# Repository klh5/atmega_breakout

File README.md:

# atmega_breakout
Breaking out the ATMega328P

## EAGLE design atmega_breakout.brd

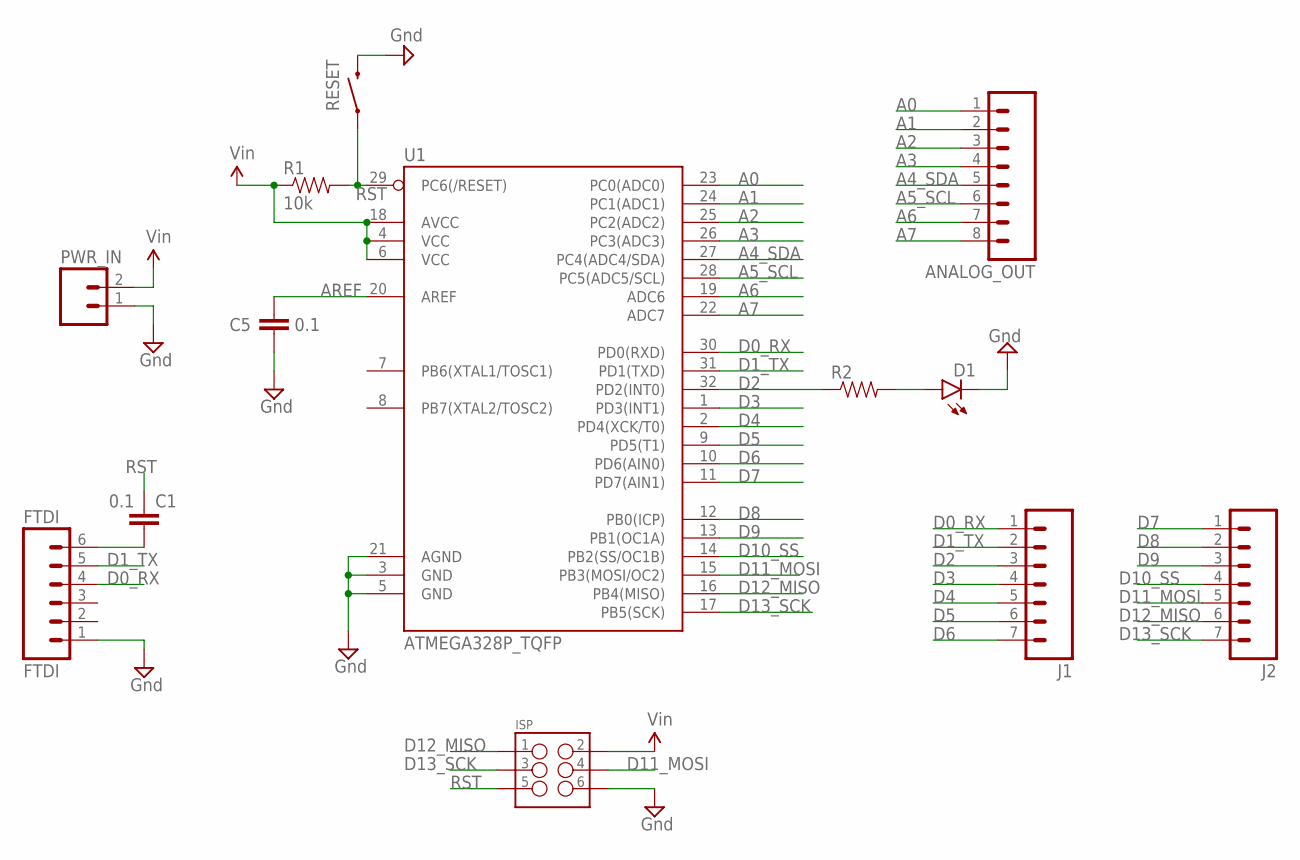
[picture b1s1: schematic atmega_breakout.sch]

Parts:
ANALOG_OUT: M08; 1X08_ROUND
C1, C5: 0.1; 1206
D1: LED1206; LED-1206
FTDI: FTDI; 1X06
ISP: M03X22X3_SILK_MALE_PTH; 2X3
J1, J2: M07; 1X07
PWR_IN: M02PTH; 1X02
R1: 10k; 1206
R2: RESISTOR1206; 1206
RESET: SWITCH-MOMENTARY-2SMD; TACTILE-SWITCH-SMD
U1: ATMEGA328P_TQFP; TQFP32-08

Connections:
A0: ANALOG_OUT.1, U1.23 (PC0(ADC0))
A1: ANALOG_OUT.2, U1.24 (PC1(ADC1))
A2: ANALOG_OUT.3, U1.25 (PC2(ADC2))
A3: ANALOG_OUT.4, U1.26 (PC3(ADC3))
A4_SDA: ANALOG_OUT.5, U1.27 (PC4(ADC4/SDA))
A5_SCL: ANALOG_OUT.6, U1.28 (PC5(ADC5/SCL))
A6: ANALOG_OUT.7, U1.19 (ADC6)
A7: ANALOG_OUT.8, U1.22 (ADC7)
AREF: C5.1, U1.20 (AREF)
D0_RX: FTDI.4, J1.1, U1.30 (PD0(RXD))
D1_TX: FTDI.5, J1.2, U1.31 (PD1(TXD))
D2: J1.3, R2.1, U1.32 (PD2(INT0))
D3: J1.4, U1.1 (PD3(INT1))
D4: J1.5, U1.2 (PD4(XCK/T0))
D5: J1.6, U1.9 (PD5(T1))
D6: J1.7, U1.10 (PD6(AIN0))
D7: J2.1, U1.11 (PD7(AIN1))
D8: J2.2, U1.12 (PB0(ICP))
D9: J2.3, U1.13 (PB1(OC1A))
D10_SS: J2.4, U1.14 (PB2(SS/OC1B))
D11_MOSI: ISP.4, J2.5, U1.15 (PB3(MOSI/OC2))
D12_MISO: ISP.1, J2.6, U1.16 (PB4(MISO))
D13_SCK: ISP.3, J2.7, U1.17 (PB5(SCK))
GND: C5.2, D1.C, FTDI.1, ISP.6, PWR_IN.1, RESET.3 (2), U1.3 (GND), U1.5 (GND), U1.21 (AGND)
unnamed: D1.A, R2.2
unnamed: C1.2, FTDI.6
RST: C1.1, ISP.5, R1.2, RESET.1, U1.29 (PC6(/RESET))
VCC: ISP.2, PWR_IN.2, R1.1, U1.4 (VCC), U1.6 (VCC), U1.18 (AVCC)

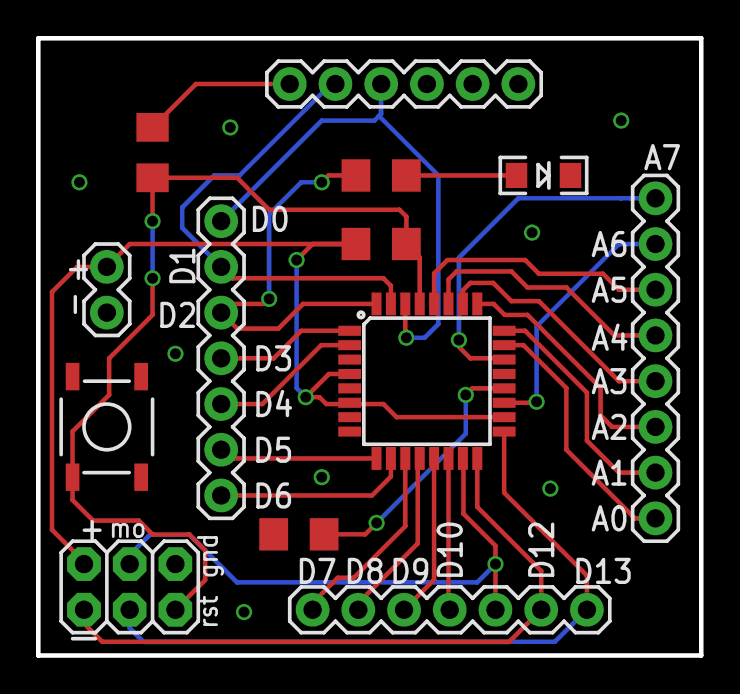
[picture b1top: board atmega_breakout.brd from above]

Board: 2 copper layers, 36.8 x 34.3 mm, 13 parts (0 on the bottom side), 28 nets.

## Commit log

2016-07-09 Adding schematic and board design
2016-07-09 Adding image
2016-07-15 Adding image link
2016-07-30 Adding gerber files

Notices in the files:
parts and their libraries:
SparkFun-DigitalIC: Licensing: Creative Commons ShareAlike 4.0 International - https://creativecommons.org/licenses/by-sa/4.0
